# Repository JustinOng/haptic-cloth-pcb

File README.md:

PCB project (Kicad 5) for light-reactive vibration modules built for [Wave 2.0](https://jus.tin.sg/wave-2-0/)

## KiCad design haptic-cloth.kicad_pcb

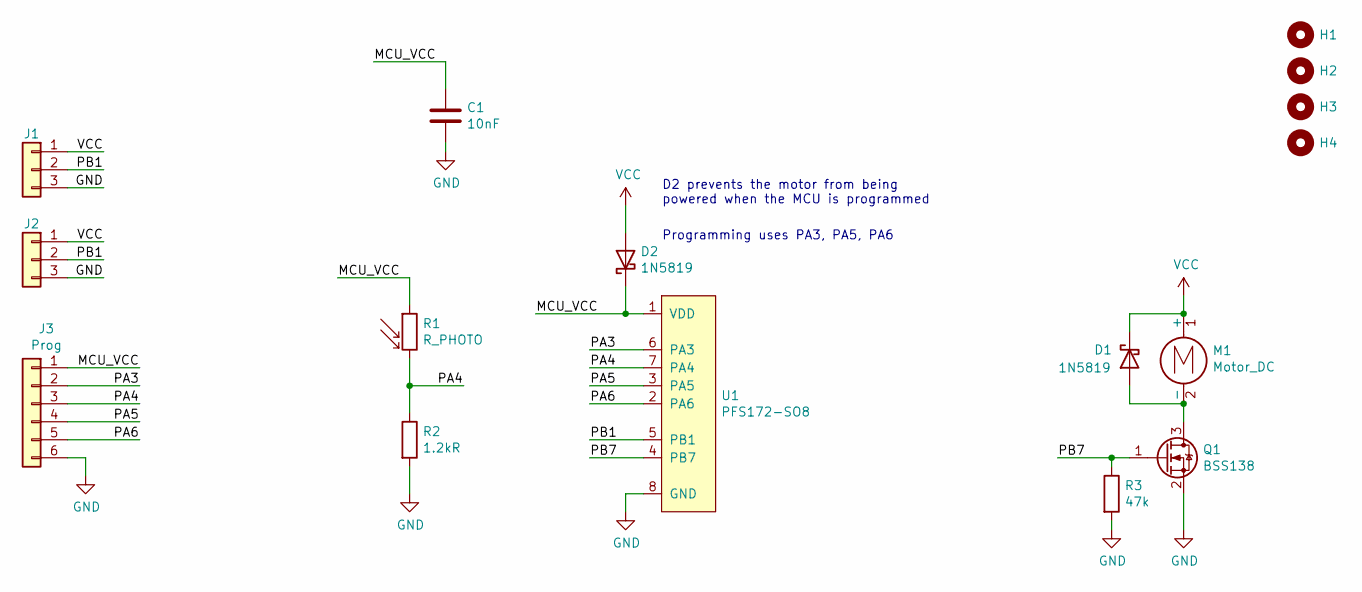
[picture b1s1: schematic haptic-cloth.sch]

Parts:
C1: 10nF; C_0603_1608Metric
D1, D2: 1N5819; D_SOD-523
H1, H2, H3, H4: MountingHole; Mounting Hole
J1, J2: Conn_01x03; JST_GH_SM03B-GHS-TB_1x03-1MP_P1.25mm_Horizontal
J3: Prog; PinHeader_1x06_P2.00mm_Vertical
M1: Motor_DC; Motor
Q1: BSS138; SOT-23
R1: R_PHOTO; R_LDR_5.1x4.3mm_P3.4mm_Vertical
R2: 1.2kR; R_0603_1608Metric
R3: 47k; R_0603_1608Metric
U1: PFS172-SO8; SO-8_3.9x4.9mm_P1.27mm

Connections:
/MCU_VCC: C1.1, D2.1 (K), J3.1, R1.1, U1.1 (VDD)
/PA3: J3.2, U1.6 (PA3)
/PA4: J3.3, R1.2, R2.1, U1.7 (PA4)
/PA5: J3.4, U1.3 (PA5)
/PA6: J3.5, U1.2 (PA6)
/PB1: J1.2, J2.2, U1.5 (PB1)
/PB7: Q1.1 (G), R3.1, U1.4 (PB7)
GND: C1.2, J1.3, J2.3, J3.6, Q1.2 (S), R2.2, R3.2, U1.8 (GND)
unnamed: D1.2 (A), M1.2 (-), Q1.3 (D)
VCC: D1.1 (K), D2.2 (A), J1.1, J2.1, M1.1 (+)

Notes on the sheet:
D2 prevents the motor from being powered when the MCU is programmed
Programming uses PA3, PA5, PA6

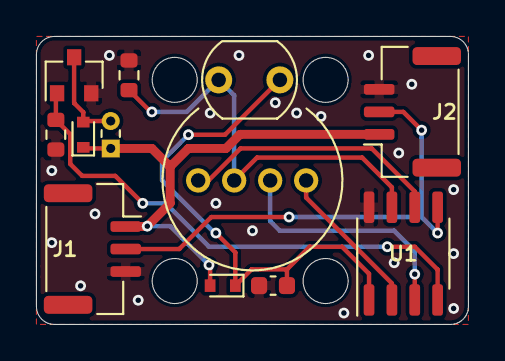
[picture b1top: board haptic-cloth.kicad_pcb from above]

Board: 2 copper layers, 24.0 x 16.0 mm, 16 parts (1 on the bottom side), 10 nets.

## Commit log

2021-11-13 Create smaller version with single connector
2021-12-09 Shift motor connector further away
2022-01-11 Fix 3D models
